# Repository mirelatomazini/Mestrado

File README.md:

# Mestrado
Repositório para adicionar os materiais usados no mestrado

Fonte da imagem da pinagem do STM32 
https://www.electronicshub.org/how-to-use-i2c-in-stm32f103c8t6/

Fonte da imagem do diagrama:
https://wiki.st.com/stm32mcu/wiki/Getting_started_with_I2C

Video onde é possível entender o basico de como a comunicacao i2c funciona: 
https://youtu.be/8yUxBn3eCGQ?si=qDOATAqDyKX4wMgh

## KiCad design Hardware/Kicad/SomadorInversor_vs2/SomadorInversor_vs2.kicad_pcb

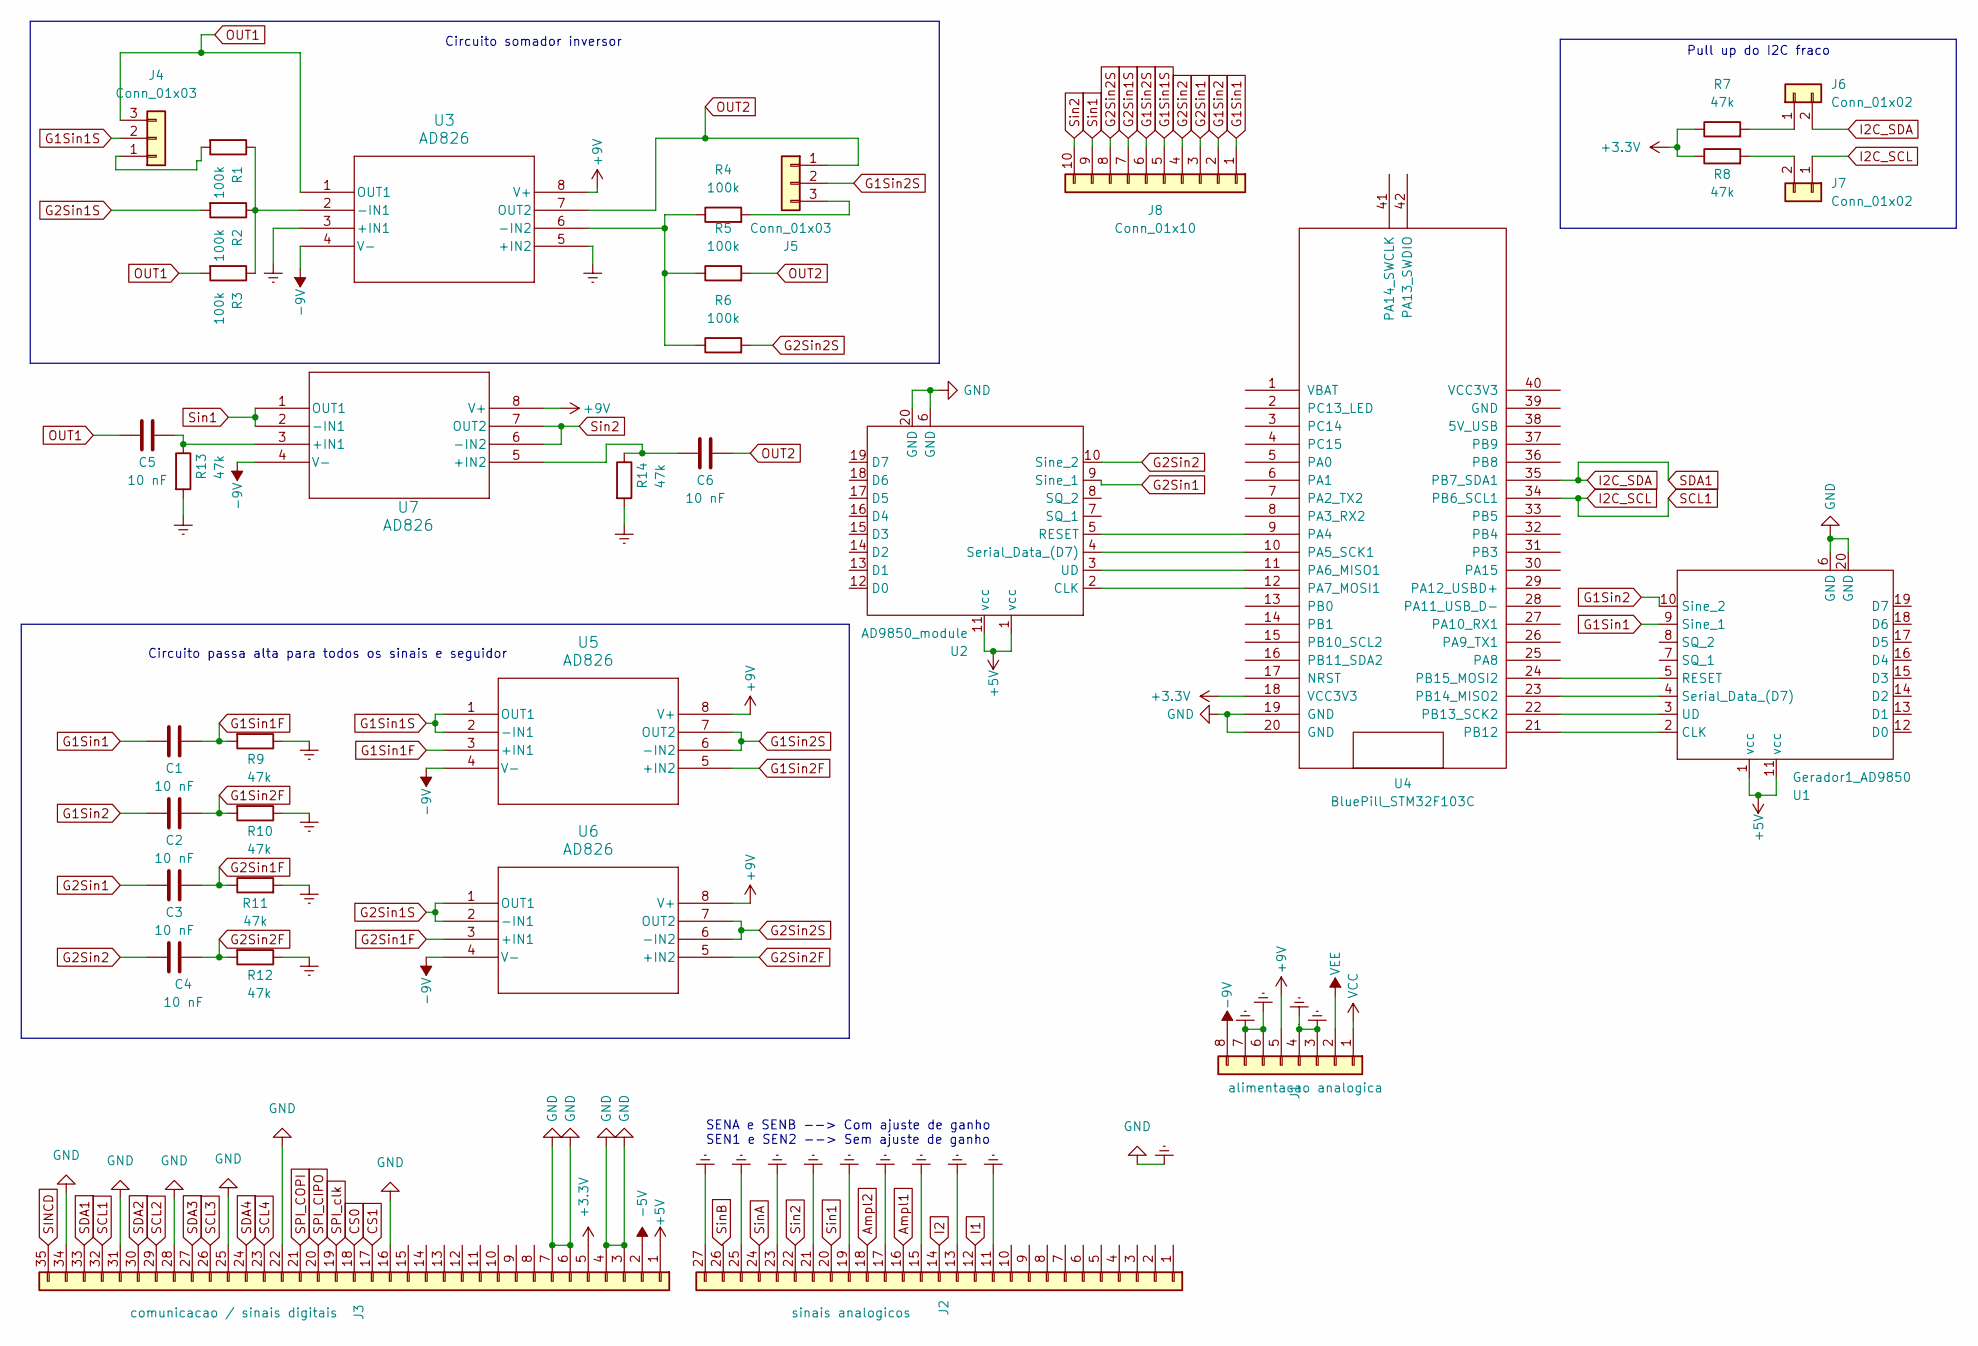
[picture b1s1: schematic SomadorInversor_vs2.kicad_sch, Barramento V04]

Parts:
C1, C2, C3, C4, C5, C6: 10 nF; CP_Radial_D5.0mm_P2.50mm
J1: alimentacao analogica; PinHeader_1x08_P2.54mm_Vertical
J2: sinais analogicos; PinHeader_1x27_P2.54mm_Vertical
J3: comunicacao / sinais digitais; PinHeader_1x35_P2.54mm_Vertical
J4, J5: Conn_01x03; PinHeader_1x03_P2.54mm_Vertical
J6, J7: Conn_01x02; PinHeader_1x02_P2.54mm_Vertical
J8: Conn_01x10; PinHeader_1x10_P2.54mm_Horizontal
R1, R2, R3, R4, R5, R6: 100k; R_Axial_DIN0207_L6.3mm_D2.5mm_P7.62mm_Horizontal
R7, R8, R9, R10, R11, R12, R13, R14: 47k; R_Axial_DIN0207_L6.3mm_D2.5mm_P7.62mm_Horizontal
U1: Gerador1_AD9850; AD9850_module
U2: AD9850_module
U3, U5, U6, U7: AD826; P8
U4: BluePill_STM32F103C

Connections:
+3.3V: J3.5, R7.1, R8.1, U4.18 (VCC3V3)
+5V: J3.1, U1.1 (vcc), U1.11 (vcc), U2.1 (vcc), U2.11 (vcc)
+9V: J1.5, U3.8 (V+), U5.8 (V+), U6.8 (V+), U7.8 (V+)
-5V: J3.2
-9V: J1.8, U3.4 (V-), U5.4 (V-), U6.4 (V-), U7.4 (V-)
Ampl1: J2.16
Ampl2: J2.18
CS0: J3.18
CS1: J3.17
Earth: J1.3, J1.4, J1.6, J1.7, J2.11, J2.13, J2.15, J2.17, J2.19, J2.21, J2.23, J2.25, J2.27, J3.3, J3.4, J3.6, J3.7, J3.16, J3.22, J3.25, J3.28, J3.31, J3.34, R9.1, R10.1, R11.2, R12.1, R13.2, R14.2, U1.6 (GND), U1.20 (GND), U2.6 (GND), U2.20 (GND), U3.3 (+IN1), U3.5 (+IN2), U4.19 (GND), U4.20 (GND)
G1Sin1: C1.1, J8.1, U1.9 (Sine_1)
G1Sin1F: C1.2, R9.2, U5.3 (+IN1)
G1Sin1S: J4.2, J8.5, U5.1 (OUT1), U5.2 (-IN1)
G1Sin2: C2.1, J8.2, U1.10 (Sine_2)
G1Sin2F: C2.2, R10.2, U5.5 (+IN2)
G1Sin2S: J5.2, J8.6, U5.6 (-IN2), U5.7 (OUT2)
G2Sin1: C3.1, J8.3, U2.9 (Sine_1)
G2Sin1F: C3.2, R11.1, U6.3 (+IN1)
G2Sin1S: J8.7, R2.2, U6.1 (OUT1), U6.2 (-IN1)
G2Sin2: C4.1, J8.4, U2.10 (Sine_2)
G2Sin2F: C4.2, R12.2, U6.5 (+IN2)
G2Sin2S: J8.8, R6.2, U6.6 (-IN2), U6.7 (OUT2)
I1: J2.12
I2: J2.14
I2C_SCL: J3.32, J7.1, U4.34 (PB6_SCL1)
I2C_SDA: J3.33, J6.2, U4.35 (PB7_SDA1)
unnamed: J4.1, R1.2
unnamed: J5.3, R4.2
unnamed: J6.1, R7.2
unnamed: J7.2, R8.2
unnamed: U1.2 (CLK), U4.21 (PB12)
unnamed: U1.5 (RESET), U4.24 (PB15_MOSI2)
unnamed: U1.4 (Serial_Data_(D7)), U4.23 (PB14_MISO2)
unnamed: U1.3 (UD), U4.22 (PB13_SCK2)
unnamed: U2.2 (CLK), U4.12 (PA7_MOSI1)
unnamed: U2.5 (RESET), U4.9 (PA4)
unnamed: U2.4 (Serial_Data_(D7)), U4.10 (PA5_SCK1)
unnamed: U2.3 (UD), U4.11 (PA6_MISO1)
unnamed: R1.1, R2.1, R3.1, U3.2 (-IN1)
unnamed: R4.1, R5.1, R6.1, U3.6 (-IN2)
unnamed: C5.2, R13.1, U7.3 (+IN1)
unnamed: C6.1, R14.1, U7.5 (+IN2)
OUT1: C5.1, J4.3, R3.2, U3.1 (OUT1)
OUT2: C6.2, J5.1, R5.2, U3.7 (OUT2)
SCL2: J3.29
SCL3: J3.26
SCL4: J3.23
SDA2: J3.30
SDA3: J3.27
SDA4: J3.24
SINCD: J3.35
SPI_CIPO: J3.20
SPI_COPI: J3.21
SPI_clk: J3.19
Sin1: J2.20, J8.9, U7.1 (OUT1), U7.2 (-IN1)
Sin2: J2.22, J8.10, U7.6 (-IN2), U7.7 (OUT2)
SinA: J2.24
SinB: J2.26
VCC: J1.1
VEE: J1.2

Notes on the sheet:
Circuito somador inversor
Pull up do I2C fraco
Circuito passa alta para todos os sinais e seguidor
SENA e SENB --> Com ajuste de ganho SEN1 e SEN2 --> Sem ajuste de ganho

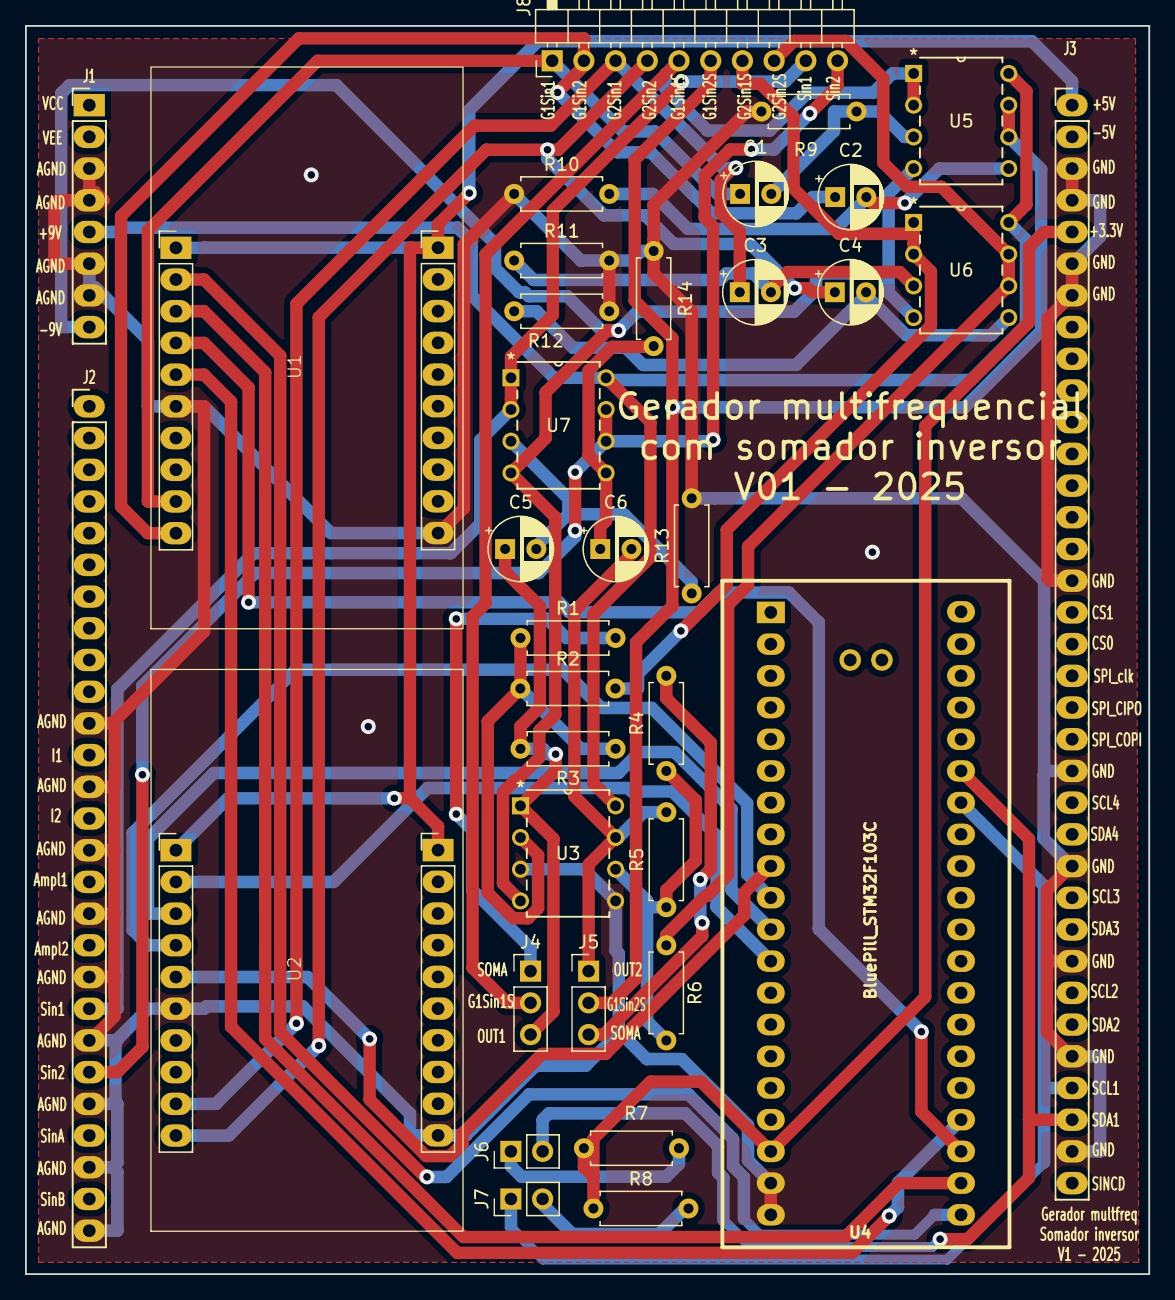
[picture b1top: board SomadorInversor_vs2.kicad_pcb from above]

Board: 2 copper layers, 90.0 x 100.0 mm, 35 parts (0 on the bottom side), 39 nets.

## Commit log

2024-09-01 Adicionado os codigo para testar comunicacao i2c entre 2 STM32
    Os codigos foram testados em setembro de 2024 e eles funcionam para testar a comunicacao entre controladores STM32
2024-09-01 Adding pinout from STM32 with i2c pins highlighted
2024-09-01 Adding Diagram for connection
2024-09-01 Update README.md
    Adicionando as informações de fontes de informação
2024-11-17 Create Projetos
    Explicação do conteúdo da pasta
2024-11-17 Add files via upload
    Projeto atualizado com CI trocado do TL072 para o AD828
2025-03-23 Placa Somador Inversor vs1
    Backup dos arquivos utilizados para gerar a placa de somador inversor para a TIE
2025-04-11 Atualizando github para vs2 da placa (impressa)
2025-04-11 Guia de montagem
2025-04-11 Backups
2025-08-04 Teste Performance na Placa Manufaturada com AD826
    Adicao do teste de performance com a placa manufaturada utilizando AD826
2026-03-16 Atualizando codigo referente a placa de aquisicao
    O codigo consta com funcao de DEBUG, comandos de medicao, retorno de dados, alteracao de frequencia e verificao de frequencias configuradas. Os comandos que podem ser enviados a partir do controlador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
2026-03-16 Envio do codigo atualizado para o controlador
    Codigo comitado possui funcao de loop e loopcompleto para varreduras consecutivas com os mesmos eletrodos de injeção ou varredura de frames completos. Também possui a explicacao dos comandos implemen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
2026-03-16 Cod. para o perifer. do gerador multifrequencial
    O codigo comitado possui a funcao de verificar as frequencias configuradas em cada um dos geradores, possui comandos para alteração das frequencias para valores pre estabelecidos e possui uma lista d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
2026-03-16 Cod. referente a placa multiplexadora
    O codigo consta com funcao de alterar os canais conectados a I1 e I2/Terra da fonte de corrente a partir de comandos enviados pelo controlador. Além disso, consta a lista de comandos disponiveis no c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
2026-03-18 Atualizacao dos arquivos utilizados para simulacao
    Upload dos arquivos SPICE do AD826 e TL072, lista de gráficos na extensão do Multisim .gra, lista de imagens e programas usados no Multsim para cada uma das simulações dos somadores
2026-03-21 Atualizando versao do controlador
    Adicionando versao do controlador com medição de corrente
2026-03-21 Atualizando pasta com codigo do multiplexador
2026-03-22 Adicionando arquivos de dados do jig resistivo
    Valores de amplitude de tensão e corrente adquiridos a partir do equipamento de TIE
2026-03-24 Dados usados para análise do circuito resistivo
2026-03-24 Dados do jig RC
2026-03-24 controlador.vs9
    controlador.vs9 possui implementada a varredura e multifrequencial simultanea
